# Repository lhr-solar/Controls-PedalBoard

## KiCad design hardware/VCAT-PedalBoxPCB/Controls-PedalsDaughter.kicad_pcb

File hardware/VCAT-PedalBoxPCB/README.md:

# Controls-PedalBoard
Pedal Daughter Board to mate with the PeripheralSOM for sensing of the linear potentiometers and brake line sensor

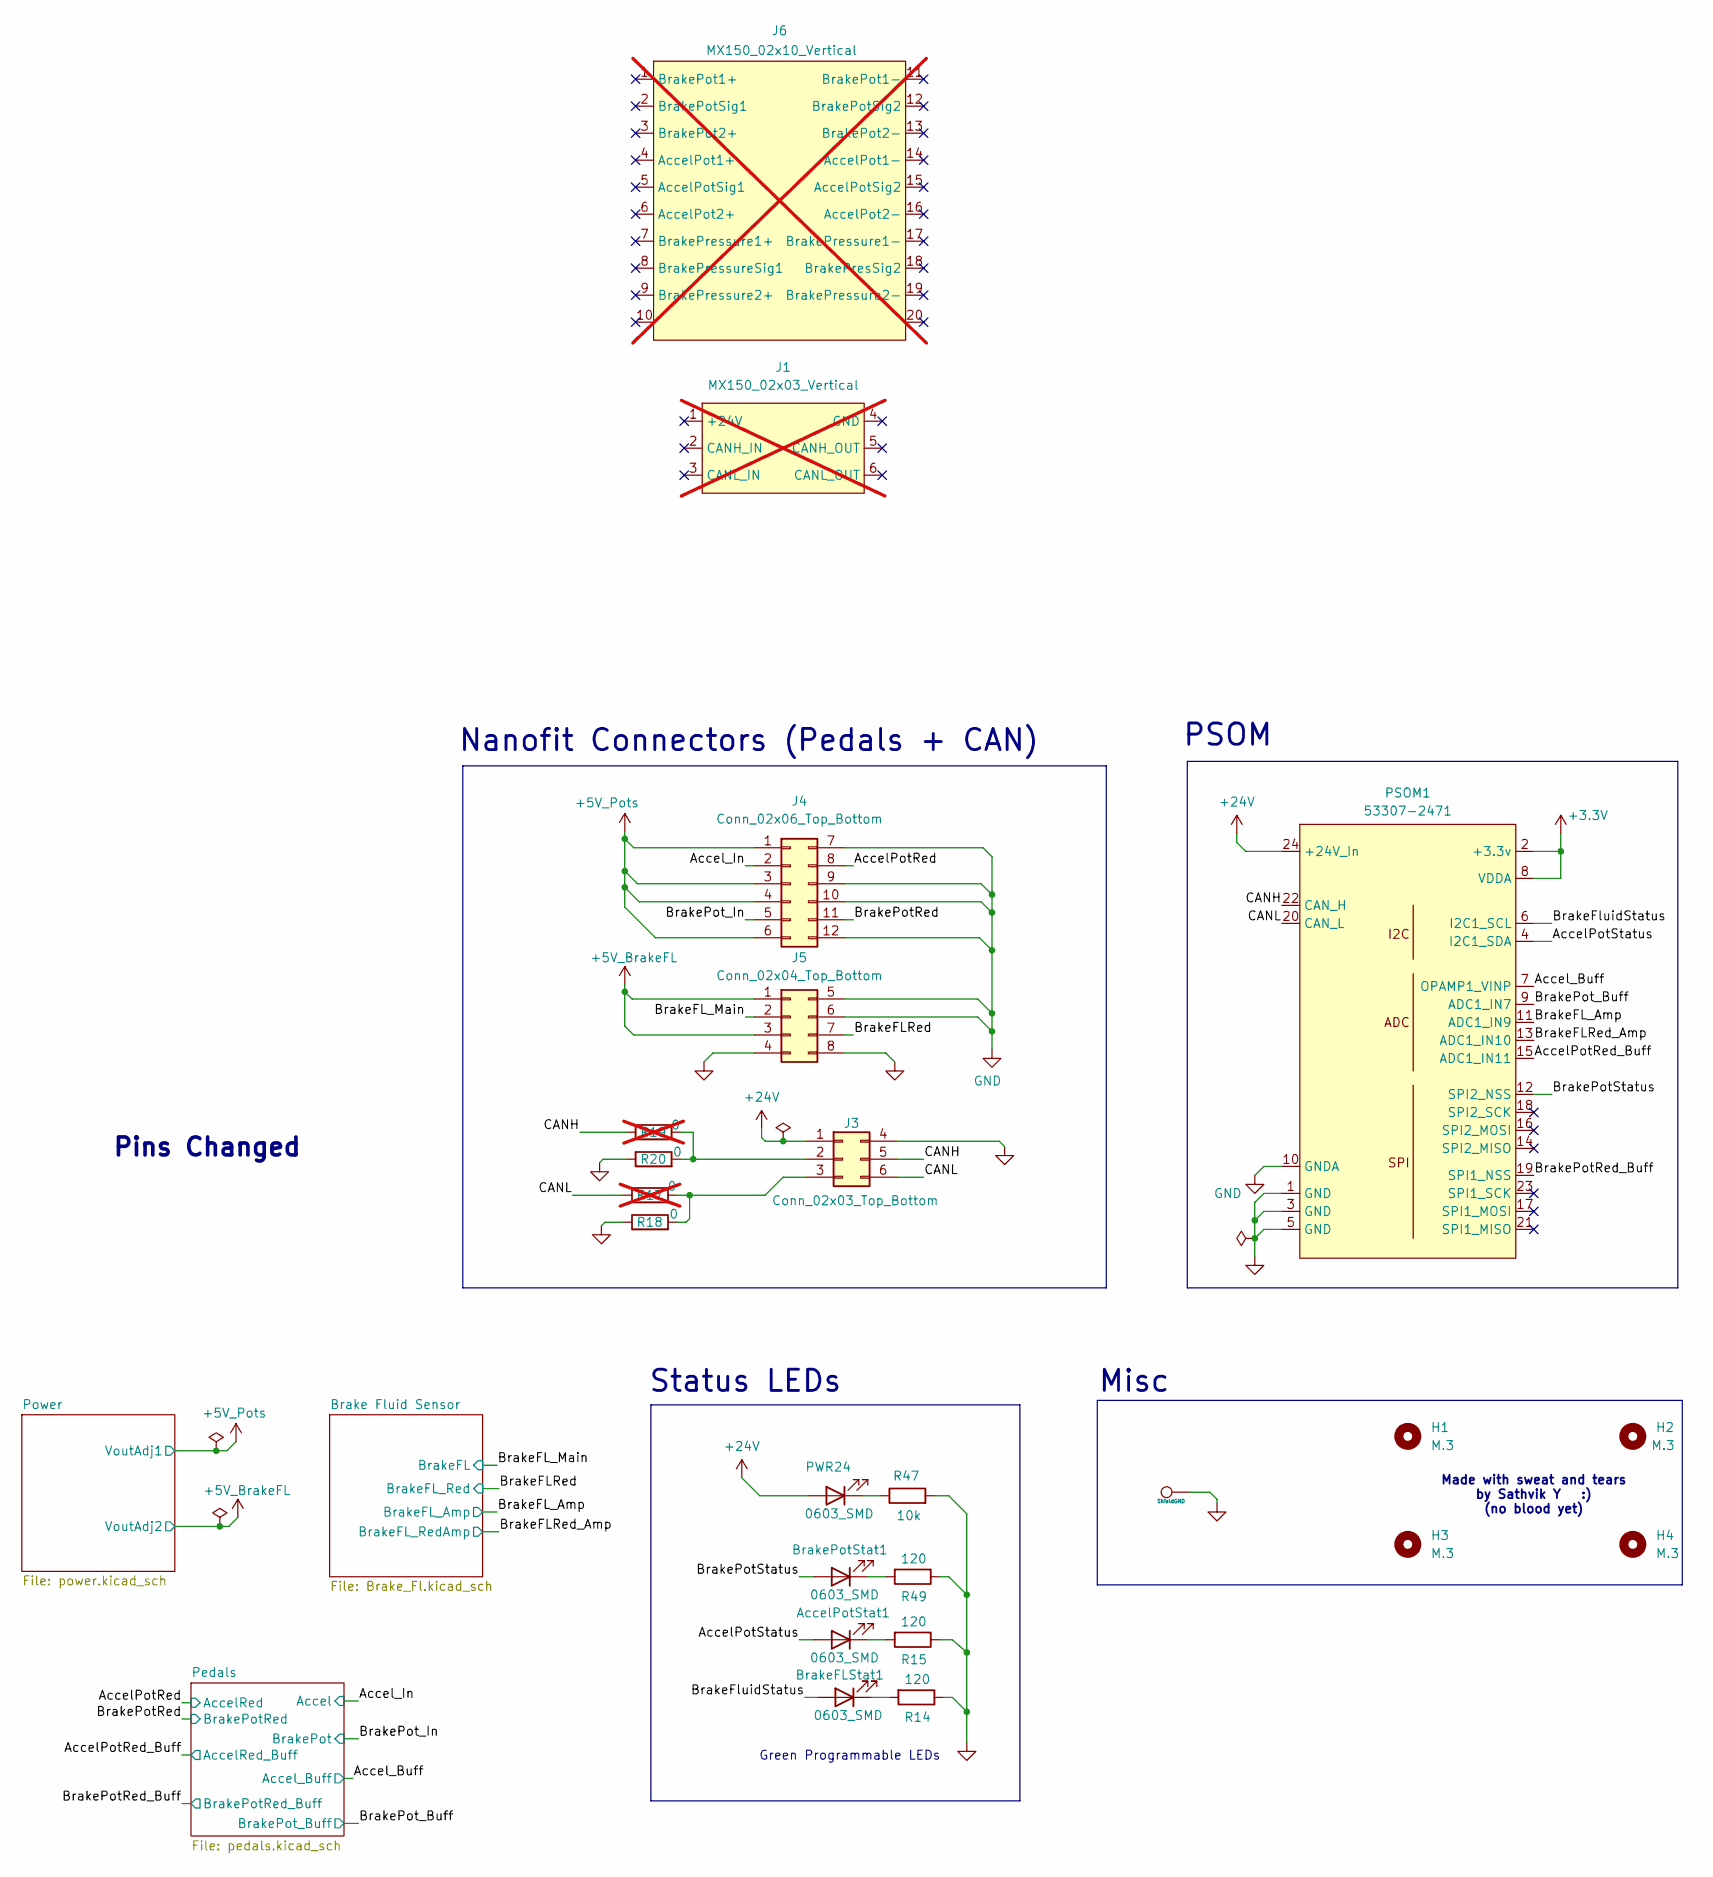
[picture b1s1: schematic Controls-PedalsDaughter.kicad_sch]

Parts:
AccelPotStat1: 0603_SMD; LED_0603_1608Metric_Pad1.05x0.95mm_HandSolder
BrakeFLStat1: 0603_SMD; LED_0603_1608Metric_Pad1.05x0.95mm_HandSolder
BrakePotStat1: 0603_SMD; LED_0603_1608Metric_Pad1.05x0.95mm_HandSolder
H1, H2, H3, H4: M.3; MountingHole_3.2mm_M3_Pad_TopBottom
J1: MX150_02x03_Vertical; not fitted
J3: Conn_02x03_Top_Bottom; Molex_Nano-Fit_105310-xx06_2x03_P2.50mm_Vertical
J4: Conn_02x06_Top_Bottom; Molex_Nano-Fit_105310-xx12_2x06_P2.50mm_Vertical
J5: Conn_02x04_Top_Bottom; Molex_Nano-Fit_105310-xx08_2x04_P2.50mm_Vertical
J6: MX150_02x10_Vertical; not fitted
PSOM1: 53307-2471; PeripheralSOM
PWR24: 0603_SMD; LED_0603_1608Metric_Pad1.05x0.95mm_HandSolder
R14, R15, R49: 120; R_0603_1608Metric_Pad0.98x0.95mm_HandSolder
R17, R19: 0; R_0603_1608Metric_Pad0.98x0.95mm_HandSolder; not fitted
R18, R20: 0; R_0603_1608Metric_Pad0.98x0.95mm_HandSolder
R47: 10k; R_0603_1608Metric_Pad0.98x0.95mm_HandSolder
Raw6: ShieldGND; TestPoint_Keystone_5005-5009_Compact

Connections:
+3.3V: PSOM1.2 (+3.3v), PSOM1.8 (VDDA); also elsewhere on the board
+5V_BrakeFL: J5.1, J5.3; also elsewhere on the board
+5V_Pots: J4.1, J4.3, J4.4, J4.6; also elsewhere on the board
+24V: J3.1, PSOM1.24 (+24V_In), PWR24.2 (A); also elsewhere on the board
/AccelPotRed: J4.8; also elsewhere on the board
/AccelPotRed_Buff: PSOM1.15 (ADC1_IN11); also elsewhere on the board
/AccelPotStatus: AccelPotStat1.2 (A), PSOM1.4 (I2C1_SDA)
/Accel_Buff: PSOM1.7 (OPAMP1_VINP); also elsewhere on the board
/Accel_In: J4.2; also elsewhere on the board
/BrakeFLRed: J5.7; also elsewhere on the board
/BrakeFLRed_Amp: PSOM1.13 (ADC1_IN10); also elsewhere on the board
/BrakeFL_Amp: PSOM1.11 (ADC1_IN9); also elsewhere on the board
/BrakeFL_Main: J5.2; also elsewhere on the board
/BrakeFluidStatus: BrakeFLStat1.2 (A), PSOM1.6 (I2C1_SCL)
/BrakePotRed: J4.11; also elsewhere on the board
/BrakePotRed_Buff: PSOM1.19 (SPI1_NSS); also elsewhere on the board
/BrakePotStatus: BrakePotStat1.2 (A), PSOM1.12 (SPI2_NSS)
/BrakePot_Buff: PSOM1.9 (ADC1_IN7); also elsewhere on the board
/BrakePot_In: J4.5; also elsewhere on the board
/CANH: J3.5, PSOM1.22 (CAN_H), R19.1
/CANL: J3.6, PSOM1.20 (CAN_L), R17.1
GND: J3.4, J4.7, J4.9, J4.10, J4.12, J5.4, J5.5, J5.6, J5.8, PSOM1.1 (GND), PSOM1.3 (GND), PSOM1.5 (GND), PSOM1.10 (GNDA), R14.1, R15.1, R18.1, R20.1, R47.2, R49.1, Raw6.1; also elsewhere on the board
unnamed: AccelPotStat1.1 (K), R15.2
unnamed: BrakeFLStat1.1 (K), R14.2
unnamed: BrakePotStat1.1 (K), R49.2
unnamed: J3.2, R19.2, R20.2
unnamed: J3.3, R17.2, R18.2
unnamed: PWR24.1 (K), R47.1

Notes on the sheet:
Made with sweat and tears by Sathvik Y :) (no blood yet)
Nanofit Connectors (Pedals + CAN)
PSOM
Green Programmable LEDs
Misc
Pins Changed
Status LEDs

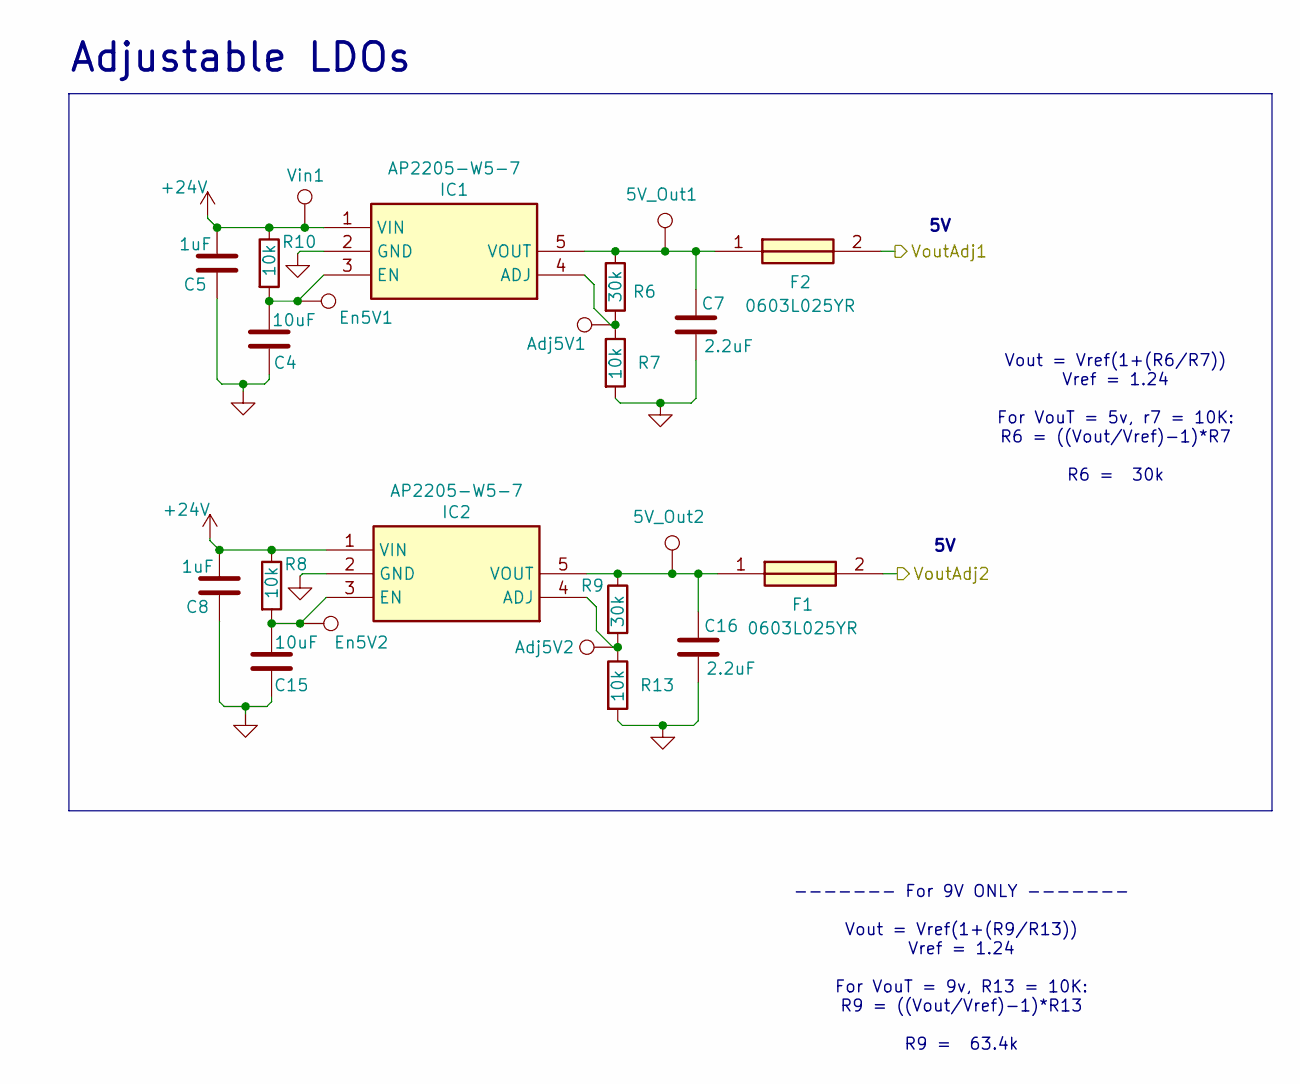
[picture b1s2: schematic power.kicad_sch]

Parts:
5V_Out1, 5V_Out2: 5V_Out; TestPoint_Pad_1.0x1.0mm
Adj5V1, Adj5V2: Adj5V; TestPoint_Pad_1.0x1.0mm
C4, C15: 10uF; C_0603_1608Metric_Pad1.08x0.95mm_HandSolder
C5, C8: 1uF; C_0603_1608Metric_Pad1.08x0.95mm_HandSolder
C7, C16: 2.2uF; C_0603_1608Metric_Pad1.08x0.95mm_HandSolder
En5V1, En5V2: Enable5V; TestPoint_Pad_1.0x1.0mm
F1, F2: 0603L025YR; FUSC1608X75N; Mouser Part Number 576-0603L025YR
IC1, IC2: AP2205-W5-7; AP2205W57; Mouser Part Number 621-AP2205-W5-7
R6, R9: 30k; R_0603_1608Metric_Pad0.98x0.95mm_HandSolder
R7, R8, R10, R13: 10k; R_0603_1608Metric_Pad0.98x0.95mm_HandSolder
Vin1: Vin; TestPoint_Pad_1.0x1.0mm

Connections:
+5V_BrakeFL: F1.2; also elsewhere on the board
+5V_Pots: F2.2; also elsewhere on the board
+24V: C5.2, C8.2, IC1.1 (VIN), IC2.1 (VIN), R8.1, R10.1, Vin1.1; also elsewhere on the board
GND: C4.1, C5.1, C7.2, C8.1, C15.1, C16.2, IC1.2 (GND), IC2.2 (GND), R7.2, R13.2; also elsewhere on the board
unnamed: Adj5V1.1, IC1.4 (ADJ), R6.2, R7.1
unnamed: C4.2, En5V1.1, IC1.3 (EN), R10.2
unnamed: 5V_Out1.1, C7.1, F2.1, IC1.5 (VOUT), R6.1
unnamed: Adj5V2.1, IC2.4 (ADJ), R9.2, R13.1
unnamed: C15.2, En5V2.1, IC2.3 (EN), R8.2
unnamed: 5V_Out2.1, C16.1, F1.1, IC2.5 (VOUT), R9.1

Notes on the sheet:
------- For 9V ONLY ------- Vout = Vref(1+(R9/R13)) Vref = 1.24 For VouT = 9v, R13 = 10K: R9 = ((Vout/Vref)-1)*R13 R9 = 63.4k
Vout = Vref(1+(R6/R7)) Vref = 1.24 For VouT = 5v, r7 = 10K: R6 = ((Vout/Vref)-1)*R7 R6 = 30k
Adjustable LDOs

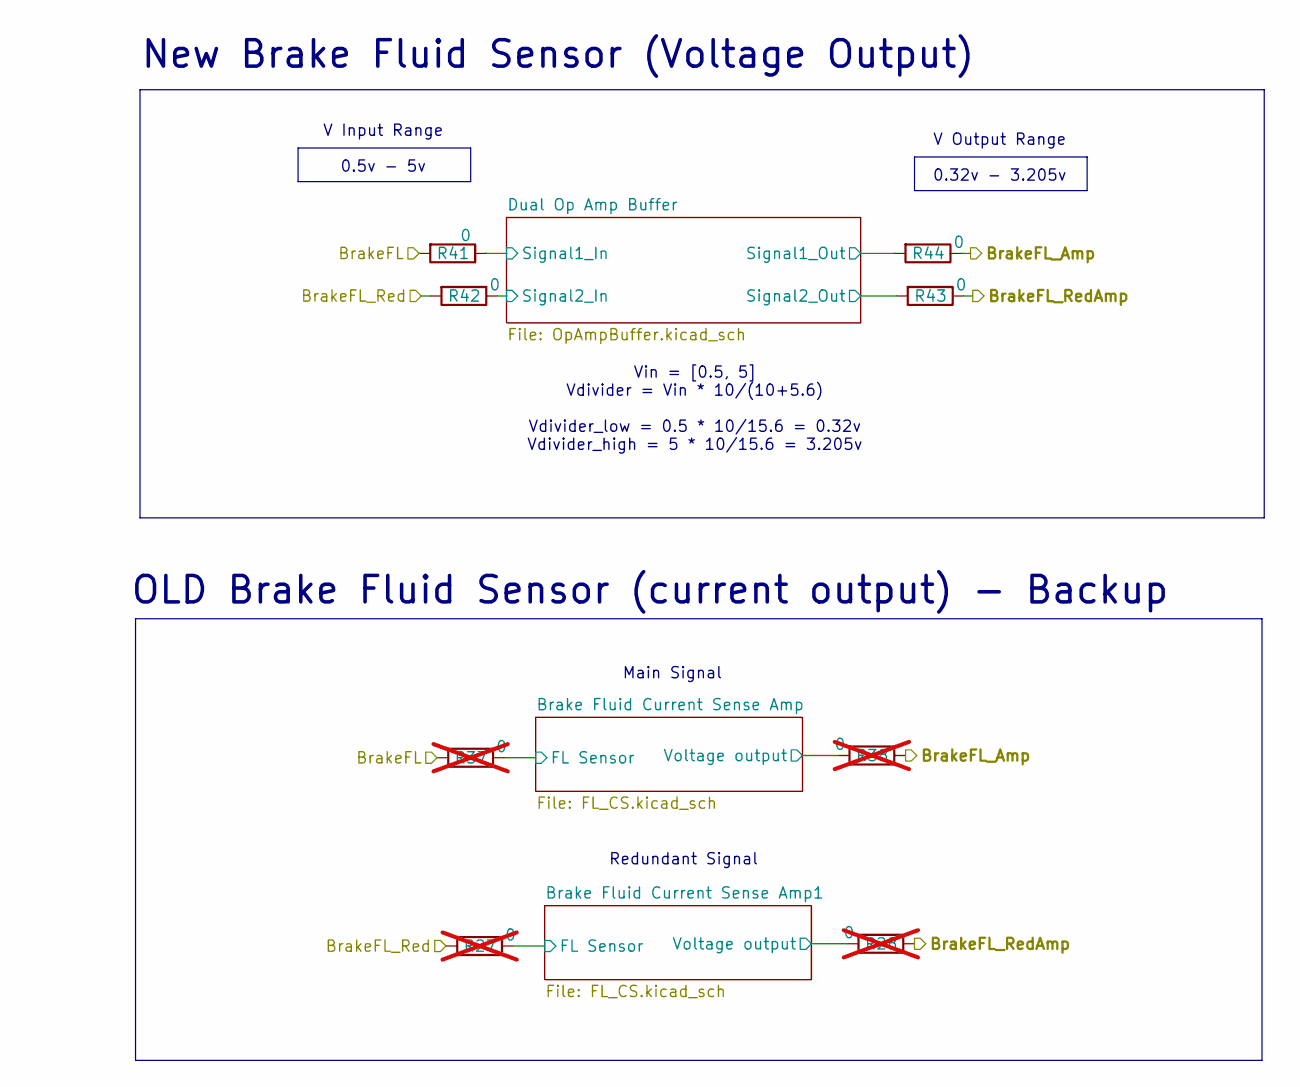
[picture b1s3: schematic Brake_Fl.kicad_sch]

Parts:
R27, R28, R37, R38: 0; R_0603_1608Metric_Pad0.98x0.95mm_HandSolder; not fitted
R41, R42, R43, R44: 0; R_0603_1608Metric_Pad0.98x0.95mm_HandSolder

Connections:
/Brake Fluid Sensor/Brake Fluid Current Sense Amp1/FL Sensor: R27.1; also elsewhere on the board
/Brake Fluid Sensor/Brake Fluid Current Sense Amp1/Voltage output: R28.2; also elsewhere on the board
/Brake Fluid Sensor/Brake Fluid Current Sense Amp/FL Sensor: R37.1; also elsewhere on the board
/Brake Fluid Sensor/Brake Fluid Current Sense Amp/Voltage output: R38.2; also elsewhere on the board
/Brake Fluid Sensor/Dual Op Amp Buffer/Signal1_In: R41.1; also elsewhere on the board
/Brake Fluid Sensor/Dual Op Amp Buffer/Signal1_Out: R44.2; also elsewhere on the board
/Brake Fluid Sensor/Dual Op Amp Buffer/Signal2_In: R42.1; also elsewhere on the board
/Brake Fluid Sensor/Dual Op Amp Buffer/Signal2_Out: R43.2; also elsewhere on the board
/BrakeFLRed: R27.2, R42.2; also elsewhere on the board
/BrakeFLRed_Amp: R28.1, R43.1; also elsewhere on the board
/BrakeFL_Amp: R38.1, R44.1; also elsewhere on the board
/BrakeFL_Main: R37.2, R41.2; also elsewhere on the board

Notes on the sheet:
New Brake Fluid Sensor (Voltage Output)
OLD Brake Fluid Sensor (current output) - Backup
V Output Range
Main Signal
0.5v - 5v
V Input Range
0.32v - 3.205v
Vin = [0.5, 5] Vdivider = Vin * 10/(10+5.6) Vdivider_low = 0.5 * 10/15.6 = 0.32v Vdivider_high = 5 * 10/15.6 = 3.205v
Redundant Signal

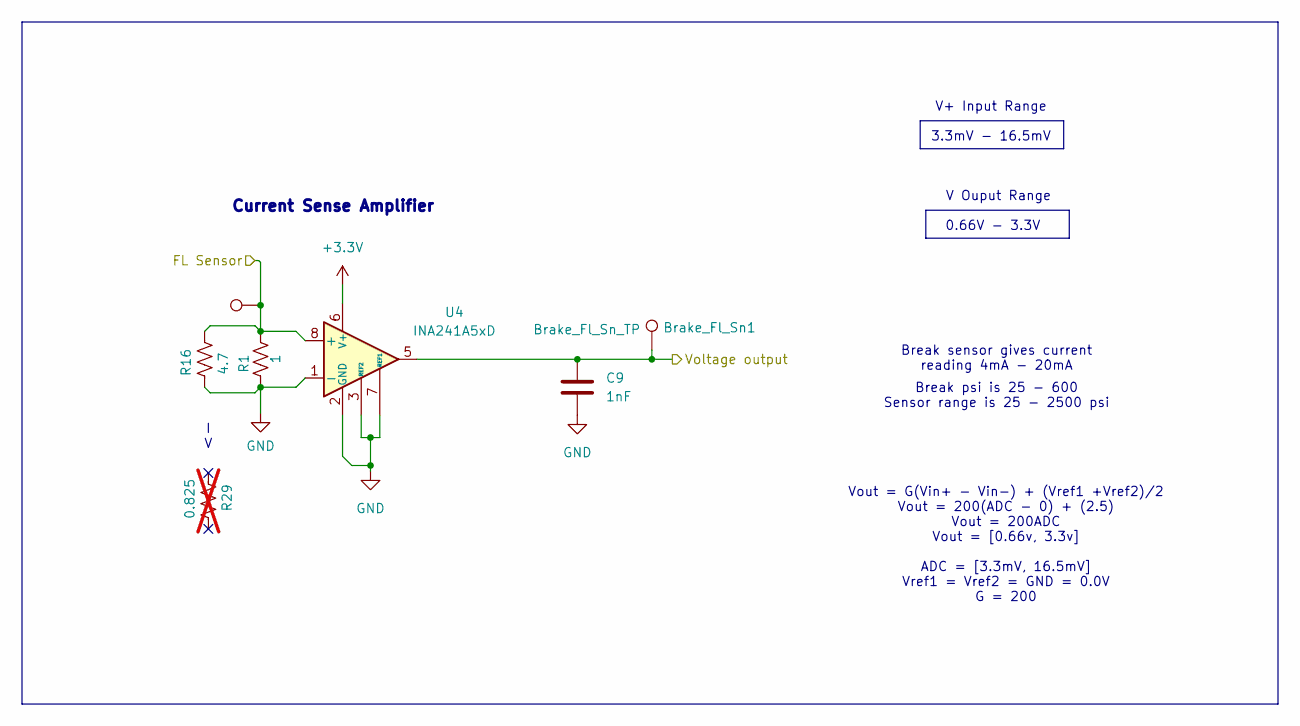
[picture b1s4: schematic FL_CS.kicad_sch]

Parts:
Brake_Fl_Sn1: Brake_Fl_Sn_TP; TestPoint_Keystone_5005-5009_Compact
C9: 1nF; C_0603_1608Metric_Pad1.08x0.95mm_HandSolder
R1: 1; R_0603_1608Metric_Pad0.98x0.95mm_HandSolder
R16: 4.7; R_0603_1608Metric_Pad0.98x0.95mm_HandSolder
R29: 0.825; R_0603_1608Metric_Pad0.98x0.95mm_HandSolder; not fitted
TP4: Raw_TP; TestPoint_Keystone_5005-5009_Compact
U4: INA241A5xD; SOIC-8_3.9x4.9mm_P1.27mm

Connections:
+3.3V: U4.6 (V+); also elsewhere on the board
/Brake Fluid Sensor/Brake Fluid Current Sense Amp/FL Sensor: R1.2, R16.2, TP4.1, U4.8 (+); also elsewhere on the board
/Brake Fluid Sensor/Brake Fluid Current Sense Amp/Voltage output: Brake_Fl_Sn1.1, C9.1, U4.5; also elsewhere on the board
GND: C9.2, R1.1, R16.1, U4.1 (-), U4.2 (GND), U4.3 (REF2), U4.4 (GND), U4.7 (REF1); also elsewhere on the board

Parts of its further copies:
Brake_Fl_Sn2: Brake_Fl_Sn_TP; TestPoint_Keystone_5005-5009_Compact
C10: 1nF; C_0603_1608Metric_Pad1.08x0.95mm_HandSolder
R30: 4.7; R_0603_1608Metric_Pad0.98x0.95mm_HandSolder
R40: 1; R_0603_1608Metric_Pad0.98x0.95mm_HandSolder
TP5: Raw_TP; TestPoint_Keystone_5005-5009_Compact
U2: INA241A5xD; SOIC-8_3.9x4.9mm_P1.27mm

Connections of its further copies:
+3.3V: U2.6 (V+); also elsewhere on the board
/Brake Fluid Sensor/Brake Fluid Current Sense Amp1/FL Sensor: R30.2, R40.2, TP5.1, U2.8 (+); also elsewhere on the board
/Brake Fluid Sensor/Brake Fluid Current Sense Amp1/Voltage output: Brake_Fl_Sn2.1, C10.1, U2.5; also elsewhere on the board
GND: C10.2, R30.1, R40.1, U2.1 (-), U2.2 (GND), U2.3 (REF2), U2.4 (GND), U2.7 (REF1); also elsewhere on the board

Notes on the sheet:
V+ Input Range
I V
Current Sense Amplifier
Vout = G(Vin+ - Vin-) + (Vref1 +Vref2)/2 Vout = 200(ADC - 0) + (2.5) Vout = 200ADC Vout = [0.66v, 3.3v] ADC = [3.3mV, 16.5mV] Vref1 = Vref2 = GND = 0.0V G = 200
V Ouput Range
0.66V - 3.3V
Break psi is 25 - 600 Sensor range is 25 - 2500 psi
3.3mV - 16.5mV
Break sensor gives current reading 4mA - 20mA

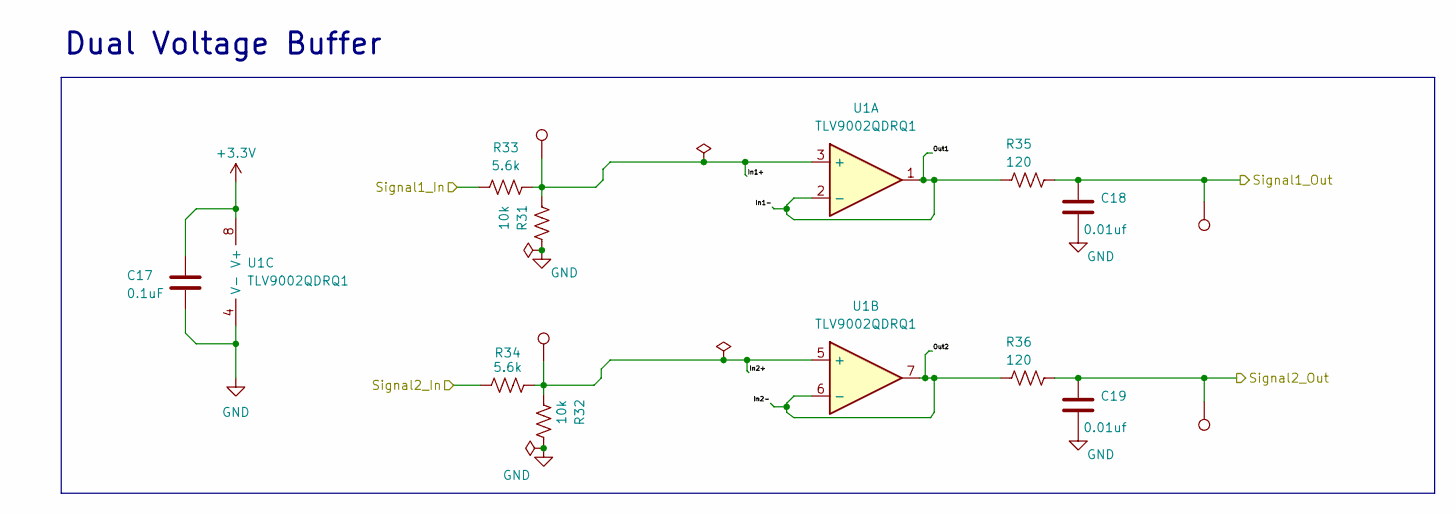
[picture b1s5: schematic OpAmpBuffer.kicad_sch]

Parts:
C17: 0.1uF; C_0603_1608Metric_Pad1.08x0.95mm_HandSolder
C18, C19: 0.01uf; C_0603_1608Metric_Pad1.08x0.95mm_HandSolder
R31, R32: 10k; R_0603_1608Metric_Pad0.98x0.95mm_HandSolder
R33, R34: 5.6k; R_0603_1608Metric_Pad0.98x0.95mm_HandSolder
R35, R36: 120; R_0603_1608Metric_Pad0.98x0.95mm_HandSolder
TP1, TP6, TP9, TP12: Raw_TP; TestPoint_Keystone_5005-5009_Compact
U1: TLV9002QDRQ1; SOIC-8_3.9x4.9mm_P1.27mm; Mouser P/N 595-TLV9002QDRQ1

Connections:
+3.3V: C17.1, U1.8 (V+); also elsewhere on the board
/Brake Fluid Sensor/Dual Op Amp Buffer/In1+: R31.2, R33.2, TP6.1, U1.3 (+)
/Brake Fluid Sensor/Dual Op Amp Buffer/In1-: R35.2, U1.1, U1.2 (-)
/Brake Fluid Sensor/Dual Op Amp Buffer/In2+: R32.2, R34.2, TP1.1, U1.5 (+)
/Brake Fluid Sensor/Dual Op Amp Buffer/In2-: R36.2, U1.6 (-), U1.7
/Brake Fluid Sensor/Dual Op Amp Buffer/Signal1_In: R33.1; also elsewhere on the board
/Brake Fluid Sensor/Dual Op Amp Buffer/Signal1_Out: C18.2, R35.1, TP9.1; also elsewhere on the board
/Brake Fluid Sensor/Dual Op Amp Buffer/Signal2_In: R34.1; also elsewhere on the board
/Brake Fluid Sensor/Dual Op Amp Buffer/Signal2_Out: C19.2, R36.1, TP12.1; also elsewhere on the board
GND: C17.2, C18.1, C19.1, R31.1, R32.1, U1.4 (V-); also elsewhere on the board

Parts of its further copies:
C1, C6: 0.1uF; C_0603_1608Metric_Pad1.08x0.95mm_HandSolder
C2, C3, C11, C12: 0.01uf; C_0603_1608Metric_Pad1.08x0.95mm_HandSolder
R2, R3, R21, R22: 5.6k; R_0603_1608Metric_Pad0.98x0.95mm_HandSolder
R4, R5, R23, R24: 10k; R_0603_1608Metric_Pad0.98x0.95mm_HandSolder
R11, R12, R25, R26: 120; R_0603_1608Metric_Pad0.98x0.95mm_HandSolder
TP2, TP3, TP7, TP8, TP10, TP11, TP13, TP14: Raw_TP; TestPoint_Keystone_5005-5009_Compact
U3, U5: TLV9002QDRQ1; SOIC-8_3.9x4.9mm_P1.27mm; Mouser P/N 595-TLV9002QDRQ1

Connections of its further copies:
+3.3V: C1.1, C6.1, U3.8 (V+), U5.8 (V+); also elsewhere on the board
/AccelPotRed: R21.1; also elsewhere on the board
/AccelPotRed_Buff: C11.2, R25.1, TP13.1; also elsewhere on the board
/Accel_Buff: C2.2, R11.1, TP7.1; also elsewhere on the board
/Accel_In: R2.1; also elsewhere on the board
/BrakePotRed: R22.1; also elsewhere on the board
/BrakePotRed_Buff: C12.2, R26.1, TP14.1; also elsewhere on the board
/BrakePot_Buff: C3.2, R12.1, TP8.1; also elsewhere on the board
/BrakePot_In: R3.1; also elsewhere on the board
/Pedals/Dual Op Amp Buffer Pots (Redundant)/In1+: R21.2, R23.2, TP10.1, U5.3 (+)
/Pedals/Dual Op Amp Buffer Pots (Redundant)/In1-: R25.2, U5.1, U5.2 (-)
/Pedals/Dual Op Amp Buffer Pots (Redundant)/In2+: R22.2, R24.2, TP11.1, U5.5 (+)
/Pedals/Dual Op Amp Buffer Pots (Redundant)/In2-: R26.2, U5.6 (-), U5.7
/Pedals/Dual Op Amp Buffer Pots (main)/In1+: R2.2, R4.2, TP2.1, U3.3 (+)
/Pedals/Dual Op Amp Buffer Pots (main)/In1-: R11.2, U3.1, U3.2 (-)
/Pedals/Dual Op Amp Buffer Pots (main)/In2+: R3.2, R5.2, TP3.1, U3.5 (+)
/Pedals/Dual Op Amp Buffer Pots (main)/In2-: R12.2, U3.6 (-), U3.7
GND: C1.2, C2.1, C3.1, C6.2, C11.1, C12.1, R4.1, R5.1, R23.1, R24.1, U3.4 (V-), U5.4 (V-); also elsewhere on the board

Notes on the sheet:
Dual Voltage Buffer

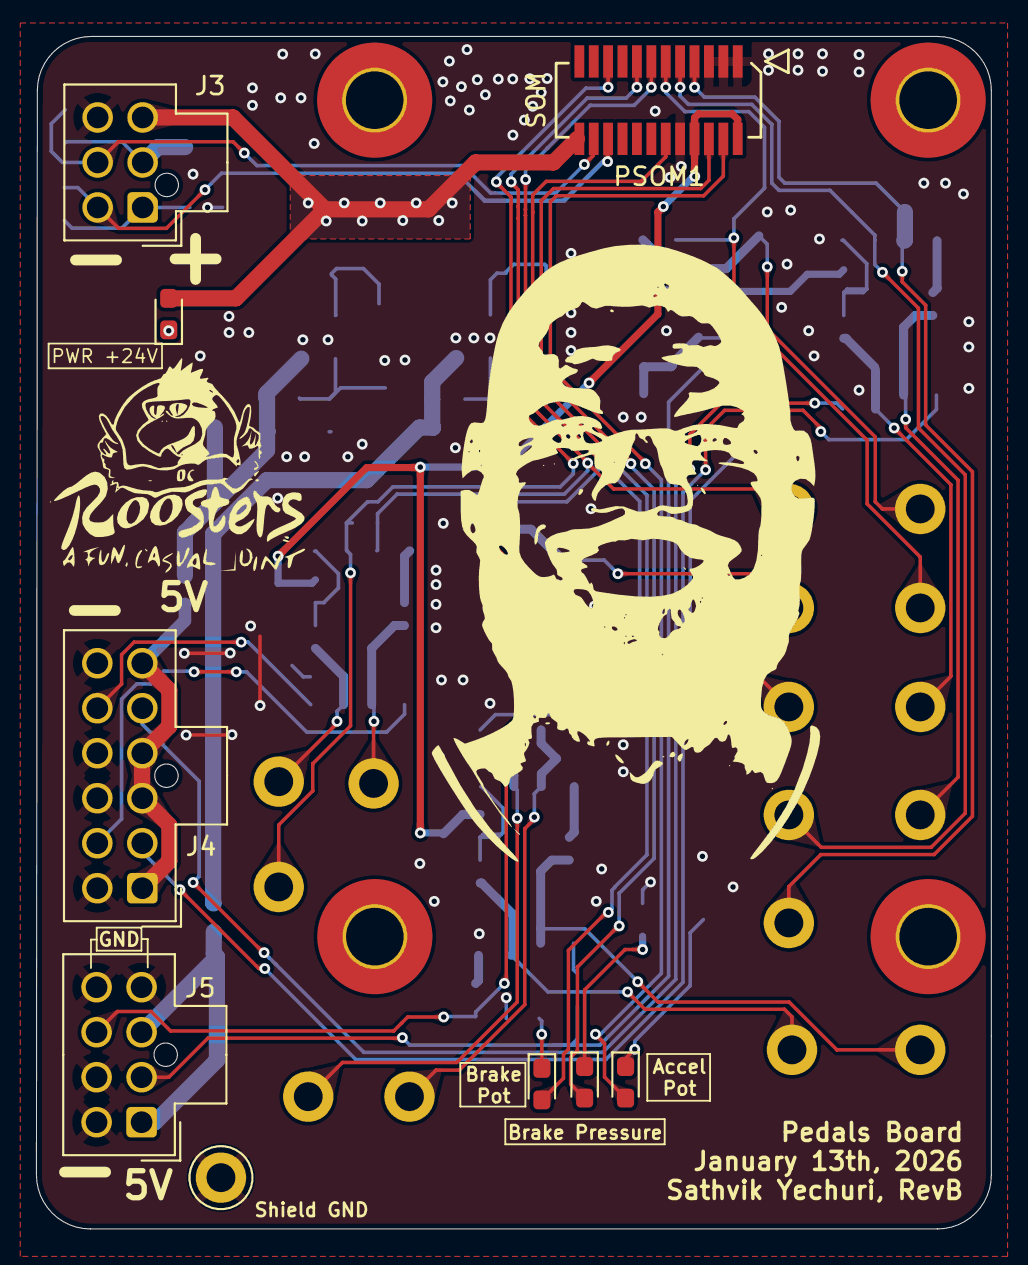
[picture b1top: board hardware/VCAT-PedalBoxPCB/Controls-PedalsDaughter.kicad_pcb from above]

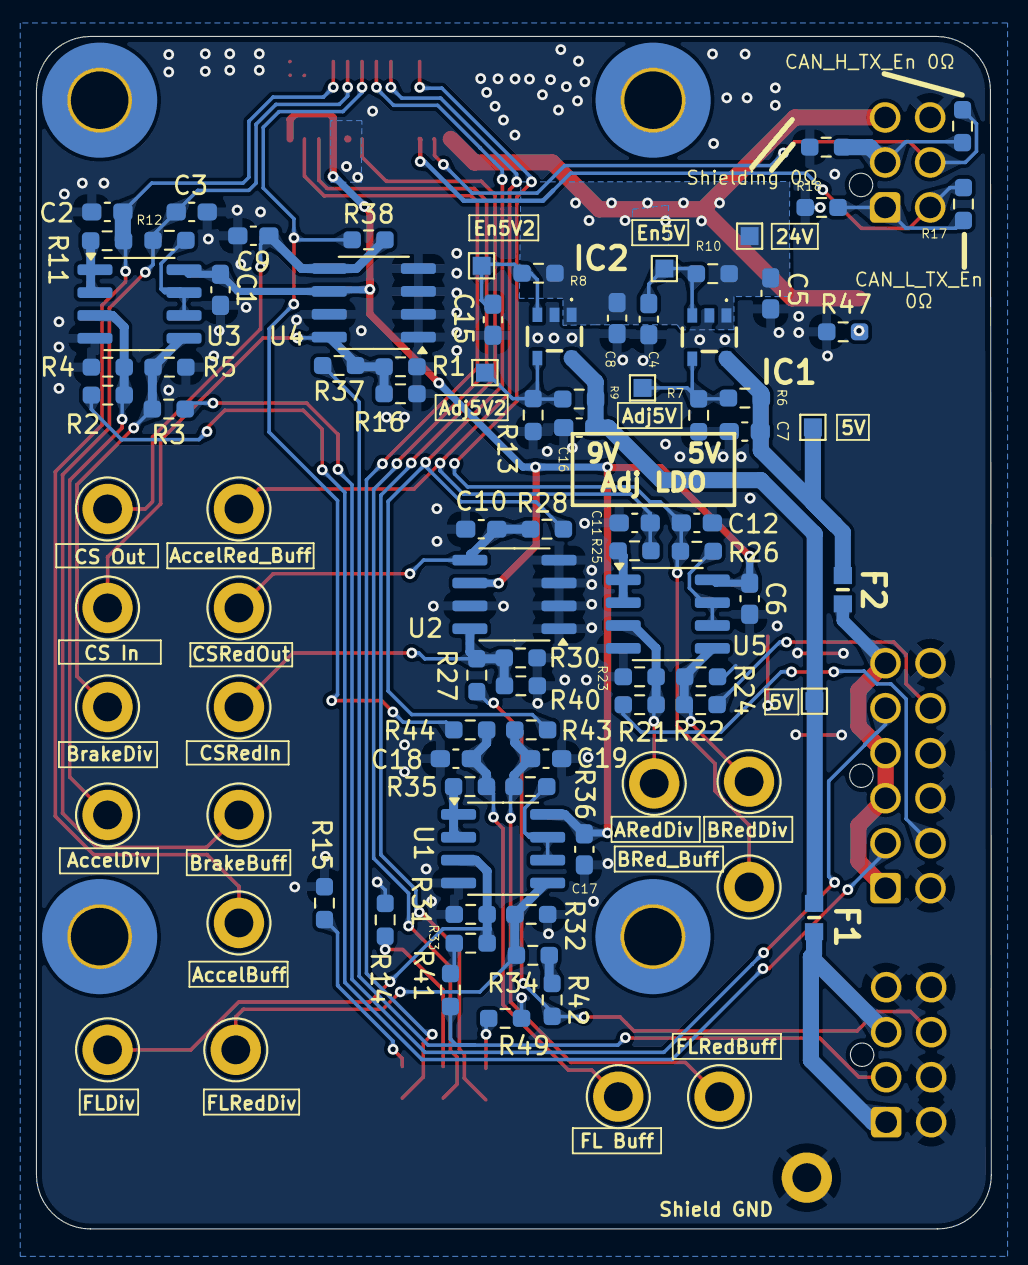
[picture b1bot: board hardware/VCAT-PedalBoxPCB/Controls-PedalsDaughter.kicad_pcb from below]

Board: 2 copper layers, 53.0 x 66.2 mm, 102 parts (93 on the bottom side), 54 nets.

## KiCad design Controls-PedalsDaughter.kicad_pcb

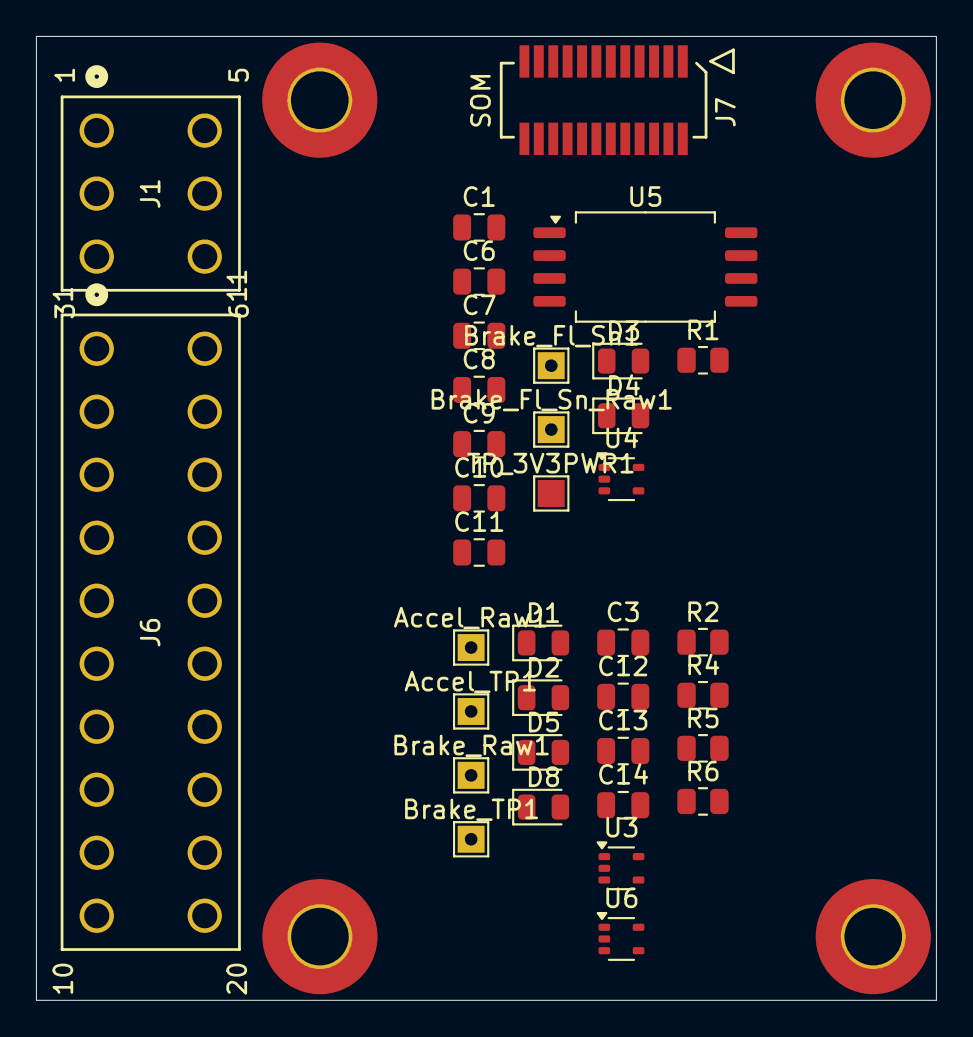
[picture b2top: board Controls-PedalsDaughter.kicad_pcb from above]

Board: 2 copper layers, 50.0 x 53.5 mm, 36 parts (0 on the bottom side), 14 nets, no tracks yet.

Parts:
Accel_Raw1: Accel_Raw_TP; TestPoint_THTPad_1.5x1.5mm_Drill0.7mm
Accel_TP1: Accel; TestPoint_THTPad_1.5x1.5mm_Drill0.7mm
Brake_Fl_Sn1: Brake_Fl_Sn_TP; TestPoint_THTPad_1.5x1.5mm_Drill0.7mm
Brake_Fl_Sn_Raw1: Brake_Fl_Sn_Raw_TP; TestPoint_THTPad_1.5x1.5mm_Drill0.7mm
Brake_Raw1: Brake_Raw_TP; TestPoint_THTPad_1.5x1.5mm_Drill0.7mm
Brake_TP1: Brake; TestPoint_THTPad_1.5x1.5mm_Drill0.7mm
C1: 100nF; C_0805_2012Metric
C3, C13: 0.1uf; C_0805_2012Metric
C6, C11: 100uF; C_0805_2012Metric
C7, C10: 1uF; C_0805_2012Metric
C8, C9: 1nF; C_0805_2012Metric
C12, C14: 1nf; C_0805_2012Metric
D1, D2, D3, D4, D5, D8: MBR; D_0805_2012Metric
J1: MX150_02x03_Vertical; CONN06_0757575131_MOL
J6: MX150_02x10_Vertical; CONN_SD-75757-002_2X10_F16p09_MOL
J7: 53307-2471; PeripheralSOM
R1: 20; R_0805_2012Metric
R2, R5: 8.2k; R_0805_2012Metric
R4, R6: 22k; R_0805_2012Metric
TP_3V3PWR1: +3V3PWR; TestPoint_Pad_1.5x1.5mm
U3, U6: TLV9301xDCK; SOT-353_SC-70-5
U4: TLV70130DBVR; SOT-353_SC-70-5
U5: AMC1300BDWV; SOIC-8_7.5x5.85mm_P1.27mm

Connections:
+3V3: D1.1 (K), D5.1 (K)
+3V3PWR: C6.1, C7.1, C8.1, TP_3V3PWR1.1, U4.5 (OUT), U5.1 (V+)
+5V: C3.2, C13.2, U3.5 (V+), U6.5 (V+)
+12V: C1.1, U4.1 (IN)
+VDDA: C10.1, C11.1, D3.1 (K), U5.8 (V+)
/Accel: Accel_TP1.1, C12.2, D1.2 (A), D2.1 (K), U3.3 (-), U3.4
/Brake Fluid Sensor/INP: Brake_Fl_Sn_Raw1.1, R1.1, U5.2 (+)
/Brake_Fl: Brake_Fl_Sn1.1, C9.1, D3.2 (A), D4.1 (K), U5.7 (+)
/Brake_Pot: Brake_TP1.1, C14.2, D5.2 (A), D8.1 (K), U6.3 (-), U6.4
GND: C3.1, C12.1, C13.1, C14.1, D2.2 (A), D8.2 (A), R4.2, R6.2, U3.2 (V-), U6.2 (V-)
GNDA: C9.2, C10.2, C11.2, D4.2 (A), U5.5 (V-), U5.6 (-)
GNDPWR: C1.2, C6.2, C7.2, C8.2, R1.2, U4.4 (GND), U5.3 (-), U5.4 (V-)
unnamed: Accel_Raw1.1, R2.1, R4.1, U3.1 (+)
unnamed: Brake_Raw1.1, R5.1, R6.1, U6.1 (+)

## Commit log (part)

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2024-10-26 Initial Commit for Pedals Board
    Break fluid pressure circuitry and excludes potentiometer for the pedal position sensor.
2024-11-02 Started Pedalboard Brakeline Fluid Sensor
2025-01-16 Added resister values
2025-01-18 Deleted Starter Project File. Should be able to open now.
2025-01-18 Added pedals
2025-01-18 Combined
2025-01-18 ERC Fixed
2025-01-18 Abt to change stuff
2025-01-18 First Draft
    ✈️
2025-01-18 Added comments
2025-01-22 Added isolation n stuff
2025-01-25 Assigned footprints for Power Sector
2025-01-25 Assigned footprints
2025-01-26 Added P/Ns
2025-01-26 Schem done, prelim pcb, added 3d models
2025-01-28 Fixed 3V3 :P
2025-01-28 again
2025-02-08 expanded board, and made all things go one way
2025-02-08 errrrrrrkereoem
2025-02-09 thanks ravi <3
2025-02-12 added space for latching
2025-02-27 routed for the first time ever
2025-02-28 Ravi <3
2025-02-28 via fix
2025-03-05 Fixed some stuff
2025-03-11 peapeapoohpooh
2025-03-11 peapeapoohpooh2
2025-03-19 Donesies?
2025-03-26 finishing touches
2025-10-11 new constraints
2025-10-14 hall effect + sub folders
2025-10-14 folder rename
2025-10-14 hardware folder
2025-10-14 submod
2025-10-14 add submod again
2025-11-01 sch too ez
2025-11-01 NOW sch review
2025-11-01 final review?? (plssss)
2025-11-01 PSOM pin layout pic
2025-11-06 pcb design review #1
2025-11-06 PCB review #2
2025-11-08 review #3
2025-11-08 review #5
2025-11-08 Lakshay approved - final review #6
2025-11-08 fillet corners
2025-11-08 updated mx150 pin order :( works now
2025-11-09 updated BOM
2025-11-13 Final review..(?)
2025-11-13 bruh
2025-11-13 bruh2
2025-11-13 LeGoat
2025-12-20 Rev B Sch updates
2026-01-05 Rev B - Initial Layout
2026-01-05 Rev B - Layout Review
2026-01-11 Layout DONEEEE
2026-01-11 uhh couple more changes, now its done
2026-01-13 Rev B Sch Review
2026-01-13 Rev B Layout #2
2026-01-14 IM DONNEEEE
2026-01-14 Gerber + JLCpcb BOM :)
2026-01-14 LDO 3d model + jlcpcb pos stuff + gerber reupload
2026-01-15 mikea
2026-01-15 change VDDA to 3v3 on sch
2026-01-15 layout fixes
2026-01-15 lcsc + prod files
2026-01-16 cleaning up files
2026-01-17 firmware init
2026-01-17 CubeMX code init
2026-01-18 Rev B - LePedals Board (#4)
    * Initial Commit for Pedals Board
    Break fluid pressure circuitry and excludes potentiometer for the pedal position sensor.
    * Started Pedalboard Brakeline Fluid Sensor
    * Added resister values
    * Deleted Starter Project File. Should be able to open now.
    * Added pedals
2026-02-25 this is some mika type shi
2026-02-28 adc is goofy
2026-03-01 breeehhh
2026-03-01 smart fella
2026-03-02 YESSSSS
2026-03-02 bye byye cubeMX
2026-03-07 Starting CAN
2026-03-10 CAN this work pls
2026-03-11 drivers done
2026-03-11 goofy ah ravi comments resolved
2026-03-11 pindefs.c
2026-03-12 can still no work - jumper didnt help
2026-03-12 lakslay changes
2026-03-14 Pots Calibration Done
2026-03-24 CAN WORKSSSS AHHHHHHHHHHHHHHHHHHHHHHHHHHHHHHHHHHHHHHHHHHHHHHHHHHHHHHHHHHH
2026-03-27 mehh
2026-03-28 the most beautiful code you'll ever see tbh
2026-03-28 goofy ah reviews addressed
2026-03-28 PLEASEEEEEEEE MERGEEEE PERMSSS
2026-03-28 Akshay changes
2026-03-28 sharepoints submodules updated
2026-04-01 shah
2026-04-01 Pedals Drivers (#5)
    * Initial Commit for Pedals Board
    Break fluid pressure circuitry and excludes potentiometer for the pedal position sensor.
    * Started Pedalboard Brakeline Fluid Sensor
    * Added resister values
    * Deleted Starter Project File. Should be able to open now.
    * Added pedals
2026-04-15 motor spin good
2026-04-16 PLEASEEEEEEEEEEEEEEEEEEEEEEEEE test ts
2026-05-05 init
2026-05-06 cleaned up lotta code; not fully tested nor documented
2026-05-07 accel tuned + pressures working prolly
2026-05-07 removed hardfault on can error
2026-05-08 match hw divider
